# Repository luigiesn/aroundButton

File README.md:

# aroundButton
A general wifi enabled button

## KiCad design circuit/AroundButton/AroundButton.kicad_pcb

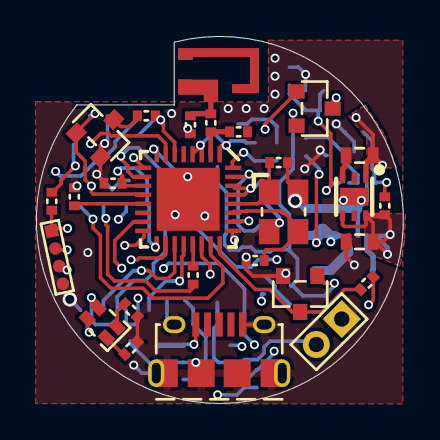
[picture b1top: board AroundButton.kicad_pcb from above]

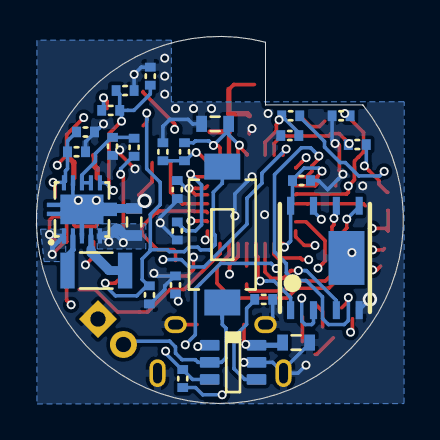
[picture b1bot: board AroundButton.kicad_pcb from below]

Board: 4 copper layers, 20.4 x 20.4 mm, 55 parts (28 on the bottom side), 42 nets.

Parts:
A1: 2450AT14A0100; CHIP_ANT_2450AT14A0100
C1, C2, C10: GRM188R60J106KE47D; CAP0603_GRM188
C3, C5: GRM188R60J226MEA0D; CAP0603_GRM188
C4, C7, C8, C9, C11, C13, C16: GCM155R71E104KE02D; CAP0402_GCM155
C6: GJM1555C1H3R0BB01D; CAP0402_GJM155
C12: GJM1555C1H5R6BB01D; CAP0402_GJM155
C14, C15: GJM1555C1H100FB01D; CAP0402_GJM155
D1: IN-S66DAT5R5B; LED0606_IN-S66DAT5R5B
D2: BAT54CLT1G; SOT23-3_BAT54CLT1G
L1: MAKK2520H1R5M; IND_2x2.5_MAKK2520H
L2, L3: NM; IND0402_GENERIC
P1: CONN_01X02_2mm; CONN_01x02_2mm
P2: 10118194-0001LF; MICRO-USB_10118194-0001LF
P3: CONN_04; CONN_01x04_1mm
Q1, Q2: IRLML2402TRPBF; SOT23-3_IRLML2402TRPBF
R1, R2, R22: ERJ-2RKF2000X; RES0402_ERJ-xR
R3, R4, R5, R6, R14: ERJ-2RKF1002X; RES0402_ERJ-xR
R7, R10: ERJ-2RKF1000X; RES0402_ERJ-xR
R8, R12: ERJ-2RKF7503X; RES0402_ERJ-xR
R9, R11, R15: ERJ-2RKF1203X; RES0402_ERJ-xR
R13: ERJ-2RKF3242X; RES0402_ERJ-xR
R16, R17, R18, R20, R21: ERJ-2RKF1202X; RES0402_ERJ-xR
SW1: PTS636SK25JSMTRLFS; 6x3.5x2.5-SWITCH_PTS636SK25JSMTRLFS
U1: BQ21040DBV; SOT23-6_BQ21040DBV
U2: TLV73333PQDRVRQ1; WSON6_TLV73333PQDRVRQ1
U3: TPS63000DRCR; VSON10_TPS63000DRCR
U4: ESP8266EX; QFN32_ESP8266EX
U5: W25Q32JVZPIM; WSON8_W25Q32JVZPIM
Y1: TSX-322526.0000MF09Z-AC3; XTAL_TSX-3225

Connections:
/3.3V: C3.1, C9.1, C10.1, C11.1, C16.1, R5.2, R6.1, R16.1, R17.2, R18.1, U2.1, U4.1, U4.3, U4.4, U4.11, U4.17, U4.29, U4.30, U5.8
/ESP8266X/50_OHM_ANT: A1.1, C12.1, L3.1
/ESP8266X/BATT_FB: C8.1, R13.1, R14.1, U4.6
/ESP8266X/BUTT_SIG: Q1.3, R6.2, U4.24
/ESP8266X/CHRG_LED: D1.2, U4.8
/ESP8266X/CHRG_SIG: R5.1, U1.3, U4.9
/ESP8266X/EN: R17.1, U4.7
/ESP8266X/FLASH_CLK: R22.1, U4.21
/ESP8266X/FLASH_CS: U4.20, U5.1
/ESP8266X/FLASH_HD: U4.18, U5.7
/ESP8266X/FLASH_MISO: U4.22, U5.2
/ESP8266X/FLASH_MOSI: U4.23, U5.5
/ESP8266X/FLASH_WP: U4.19, U5.3
/ESP8266X/GPIO0_~DOWNLOAD: P3.1, R18.2, U4.15
/ESP8266X/GPIO15: R20.1, U4.13
/ESP8266X/PWR_HOLD: D2.1, U4.16
/ESP8266X/RXD: P3.3, U4.25
/ESP8266X/STATUS_LED: D1.4, U4.10
/ESP8266X/TXD: P3.2, U4.26
/ESP8266X/XTAL_IN: C14.1, U4.28, Y1.1
/ESP8266X/XTAL_OUT: C15.1, U4.27, Y1.3
/ESP8266X/~RST: C13.2, R16.2, U4.32
/GND: C1.2, C2.2, C3.2, C4.2, C5.2, C6.2, C7.2, C8.2, C9.2, C10.2, C11.2, C13.1, C14.2, C15.2, C16.2, L2.2, L3.2, P1.1, P2.5, P2.6, P3.4, Q1.2, Q2.2, R1.2, R2.2, R3.2, R4.2, R9.2, R11.2, R12.2, R15.1, R20.2, R21.2, U1.5, U2.3, U2.7, U3.3, U3.9, U3.11, U4.33, U5.4, U5.TP, Y1.2, Y1.4
/Power/3.6V: C5.1, R8.1, U2.4, U2.6, U3.1
/Power/BATT_FB_EN: Q2.1, R15.2, U4.12
/Power/BUTT_INPUT: D2.2, Q1.1, R9.1, SW1.2
/Power/CHRGR_IN: C1.1, P2.1, U1.6
/V_BATT: C2.1, P1.2, R7.2, R13.2, SW1.1, U1.2, U3.5
unnamed: C4.1, R7.1, U3.7, U3.8
unnamed: C6.1, R8.2, R11.1, U3.10
unnamed: C7.1, R10.1, R12.1, U3.6
unnamed: C12.2, L2.1, U4.2
unnamed: D1.1, R1.1
unnamed: D1.3, R2.1
unnamed: D2.3, R10.2
unnamed: L1.1, U3.4
unnamed: L1.2, U3.2
unnamed: Q2.3, R14.2
unnamed: R3.1, U1.4
unnamed: R4.1, U1.1
unnamed: R21.1, U4.31
unnamed: R22.2, U5.6

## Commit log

2019-08-05 Primeiro commit com layout em fase de finalização
2019-08-05 Layout finalizado
2019-08-05 Modificações na biblioteca
    - Inclusão de modelos 3d
    - Atualização do layout
2019-08-06 Atlerações gerais no layout
